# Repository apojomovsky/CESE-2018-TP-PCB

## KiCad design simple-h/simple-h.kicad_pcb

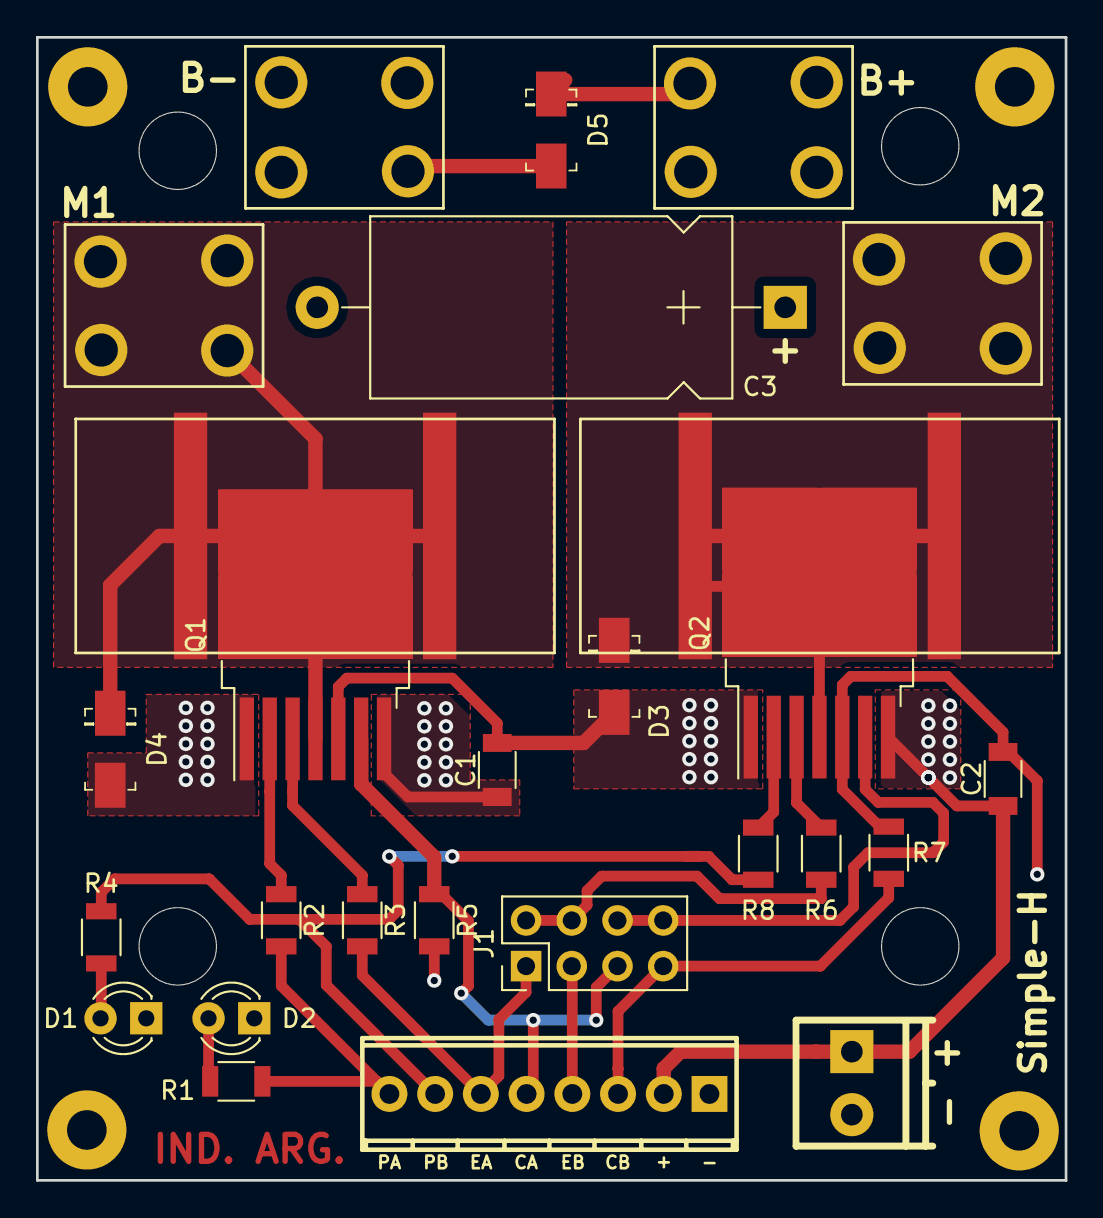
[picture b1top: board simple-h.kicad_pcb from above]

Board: 2 copper layers, 57.2 x 63.5 mm, 35 parts (0 on the bottom side), 18 nets.

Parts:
C1, C2: 1uF 25V; C_1206
C3: 470uF 35V; CP_Axial_L20.0mm_D10.0mm_P26.00mm_Horizontal
D1, D2: LED; LED_D3.0mm
D3, D4, D5: D_Schottky; DO-214AC_custom
HS1, HS2: Heatsink_Pad; Heatsink_AAVID_573300D00010G_TO-263
J1: Conn_02x04_Odd_Even; Pin_Header_Straight_2x04_Pitch2.54mm
J2: CN1; mpt_0,5%2f8-2,54
J3: FAN; pt_1,5-2-3,5-h
J4: M1; keystone_7693
J5: M2; keystone_7693
J6: B+; keystone_7693
J7: B-; keystone_7693
MH1, MH2, MH3, MH4: MountingHole; MountingHole_2.2mm_M2_Pad
MH5, MH6, MH7, MH8: MountingHole; MountingHole_4.3mm_M4
Q1, Q2: BTS7960B; TO-263-7_TabPin8
R1, R4: 220; R_1206
R2, R3, R6, R8: 10K; R_1206
R5, R7: 634; R_1206

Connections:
/CURR-A: J1.5, J2.5, Q1.6, R5.1
/CURR-B: J1.7, J2.3, R7.2
/EN-A: J1.1, J2.6, R3.2
/EN-B: J1.3, J2.4
/M1: D4.1, HS1.1, J4.1, Q1.4, Q1.8
/M2: D3.1, HS2.1, J5.1, Q2.4, Q2.8
/PWM-A: J2.8, R1.1, R2.2
/PWM-B: J2.7, R4.1, R8.2
GND: C1.2, C2.2, C3.2, D1.1, D2.1, D3.2, D4.2, D5.2, J2.1, J3.2, J7.1, Q1.1, Q1.5, Q2.1, Q2.5, R5.2, R7.1
unnamed: D1.2, R4.2
unnamed: D2.2, R1.2
unnamed: J1.2, J1.4, R6.2
unnamed: J1.6, J1.8, Q2.6
unnamed: Q1.2, R2.1
unnamed: Q1.3, R3.1
unnamed: Q2.2, R8.1
unnamed: Q2.3, R6.1
VDD: C1.1, C2.1, C3.1, D5.1, J2.2, J3.1, J6.1, Q1.7, Q2.7

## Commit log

2018-09-24 Se agrego esquematico original
2018-10-10 Agregue footprints
2018-10-19 Ruteo terminado
2018-10-26 Se agregaron modelos 3D
2018-10-26 Se agregaron los modelos 3D al proyecto
2018-10-26 Se agregaron comentarios
2018-10-26 Se agregaron todos los footprints al proyecto
2018-10-26 Se eliminaron archivos innecesarios
2018-10-26 Se modificaron los paths a los modelos 3D locales
2018-10-28 Se agregaron fiduciales
2018-11-03 Se aplicaron correcciones basadas en revision
